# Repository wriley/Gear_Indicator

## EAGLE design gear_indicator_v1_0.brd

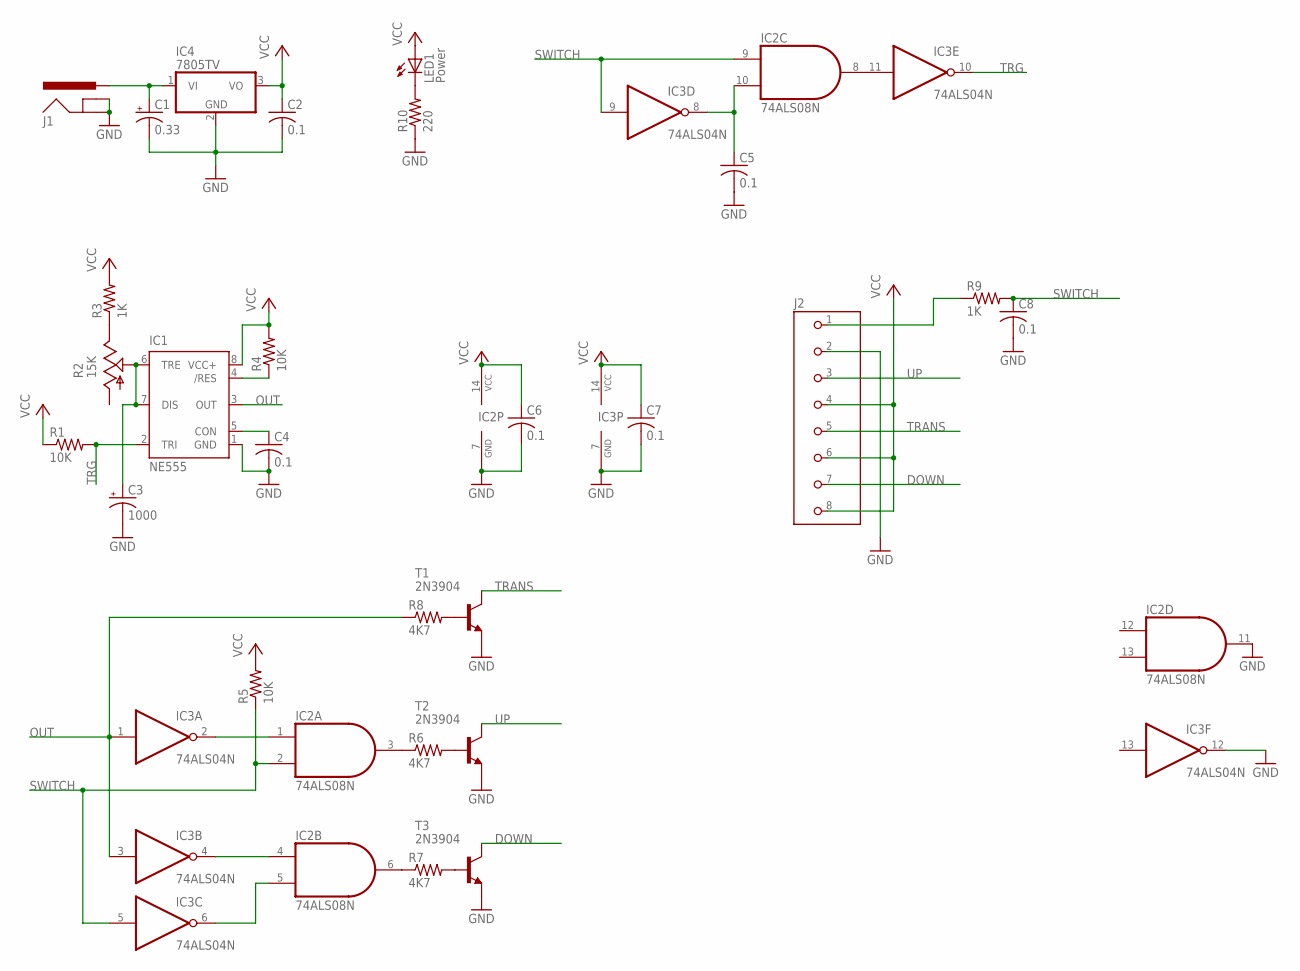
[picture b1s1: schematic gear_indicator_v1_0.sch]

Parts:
C1: 0.33; E2,5-6
C2, C4, C5, C6, C7, C8: 0.1; C025-025X050
C3: 1000; E3,5-10
IC1: NE555; DIL-08
IC2: 74ALS08N; DIL14
IC3: 74ALS04N; DIL14
IC4: 7805TV; TO220V
J1: POWER_JACKPTH; POWER_JACK_PTH
J2: TERMBLOCKX8
LED1: Power; LED-3MM
R1, R4, R5: 10K; 0207/7
R2: 15K; B25P
R3, R9: 1K; 0207/7
R6, R7, R8: 4K7; 0207/7
R10: 220; 0207/7
T1, T2, T3: 2N3904; TO92

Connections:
DOWN: J2.7, T3.1 (C)
GND: C1.-, C2.2, C3.-, C4.2, C5.2, C6.2, C7.2, C8.2, IC1.1 (GND), IC2.7 (GND), IC2.11 (O), IC3.7 (GND), IC3.12 (O), IC4.2 (GND), J1.GND, J1.GNDBREAK, J2.2, R10.1, T1.3 (E), T2.3 (E), T3.3 (E)
unnamed: R2.E, R3.1
unnamed: C3.+, IC1.6 (TRE), IC1.7 (DIS), R2.S
unnamed: IC1.4 (/RES), R4.1
unnamed: C4.1, IC1.5 (CON)
unnamed: IC2.1 (I0), IC3.2 (O)
unnamed: IC2.4 (I0), IC3.4 (O)
unnamed: IC2.5 (I1), IC3.6 (O)
unnamed: IC2.3 (O), R6.1
unnamed: IC2.6 (O), R7.1
unnamed: R8.2, T1.2 (B)
unnamed: R6.2, T2.2 (B)
unnamed: C1.+, IC4.1 (VI), J1.PWR
unnamed: R7.2, T3.2 (B)
unnamed: IC2.8 (O), IC3.11 (I)
unnamed: C5.1, IC2.10 (I1), IC3.8 (O)
unnamed: LED1.K (C), R10.2
unnamed: J2.1, R9.1
OUT: IC1.3 (OUT), IC3.1 (I), IC3.3 (I), R8.1
SWITCH: C8.1, IC2.2 (I1), IC2.9 (I0), IC3.5 (I), IC3.9 (I), R5.1, R9.2
TRANS: J2.5, T1.1 (C)
TRG: IC1.2 (TRI), IC3.10 (O), R1.2
UP: J2.3, T2.1 (C)
VCC: C2.1, C6.1, C7.1, IC1.8 (VCC+), IC2.14 (VCC), IC3.14 (VCC), IC4.3 (VO), J2.4, J2.6, J2.8, LED1.A, R1.1, R3.2, R4.2, R5.2

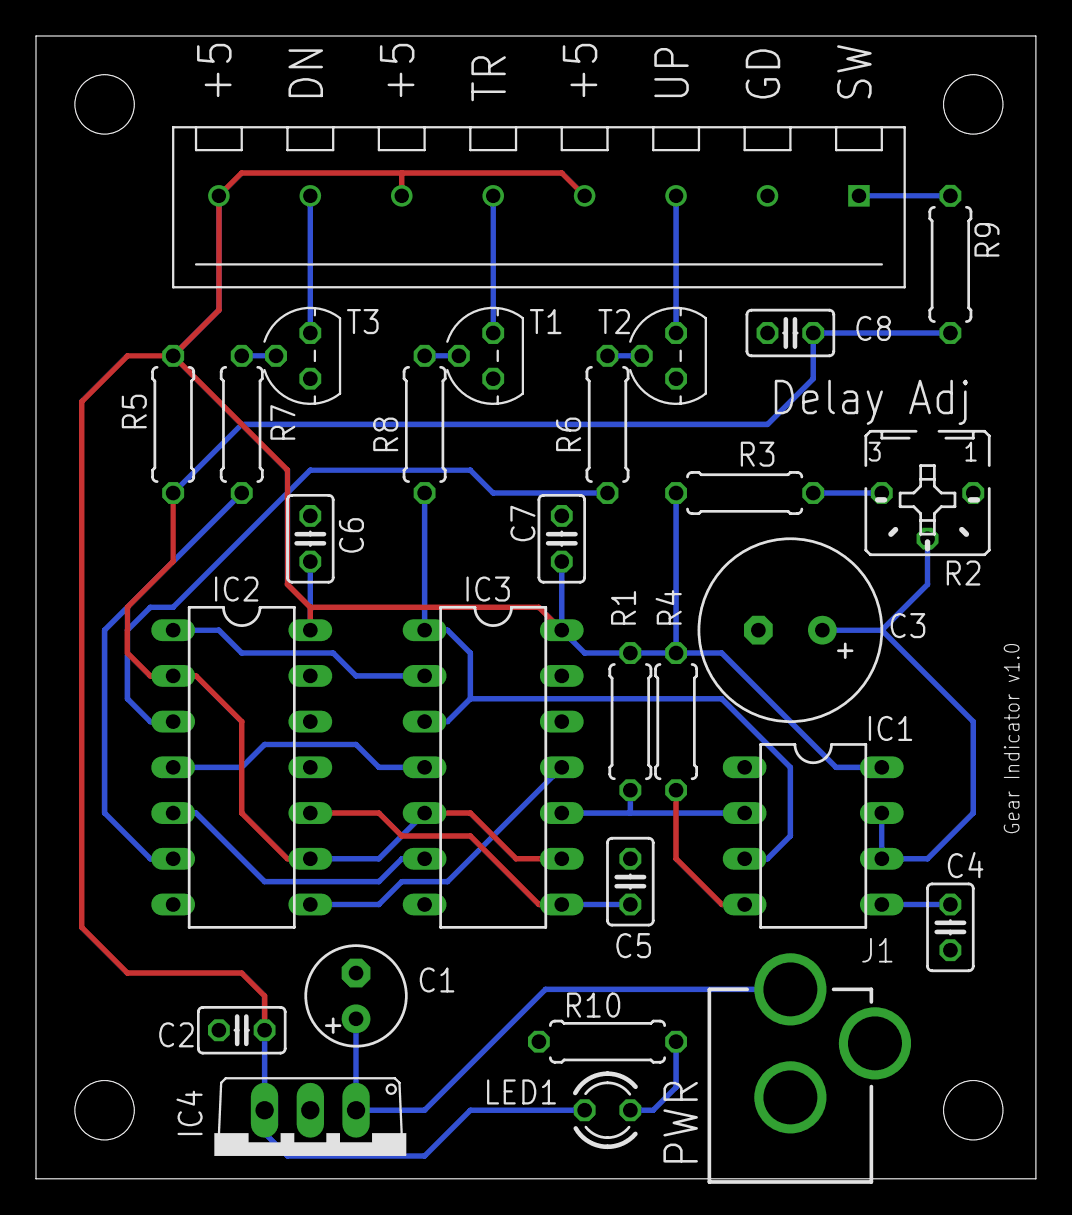
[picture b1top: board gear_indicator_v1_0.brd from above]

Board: 2 copper layers, 55.5 x 63.5 mm, 32 parts (0 on the bottom side), 25 nets.

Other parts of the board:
U$1, U$2, U$3, U$4: STAND-OFF

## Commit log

2009-10-01 initial import
2009-10-01 added schematic and image
2009-10-01 gear_indicator_v1_0.sch: added open collector outputs gear_indicator_v1_0.brd: added PCB updated schematic image
2009-10-01 added images for schematic and pcb added POVRay file
2012-01-15 smaller board, layout tweaks
2012-01-16 Fixed tie to ground for unused logic gates Added low pass filter on switch input
2012-01-16 layout tweaks
2012-01-16 added .mpd for eagle3d
2012-01-18 silkscreen updates
2012-01-19 povray files update
2012-01-19 pcb povray file update
